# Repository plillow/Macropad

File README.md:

# Macropad
My Macropad, First time ever creating something 
3 keys to be used for anything
Cad image

Pcb 
Schematic

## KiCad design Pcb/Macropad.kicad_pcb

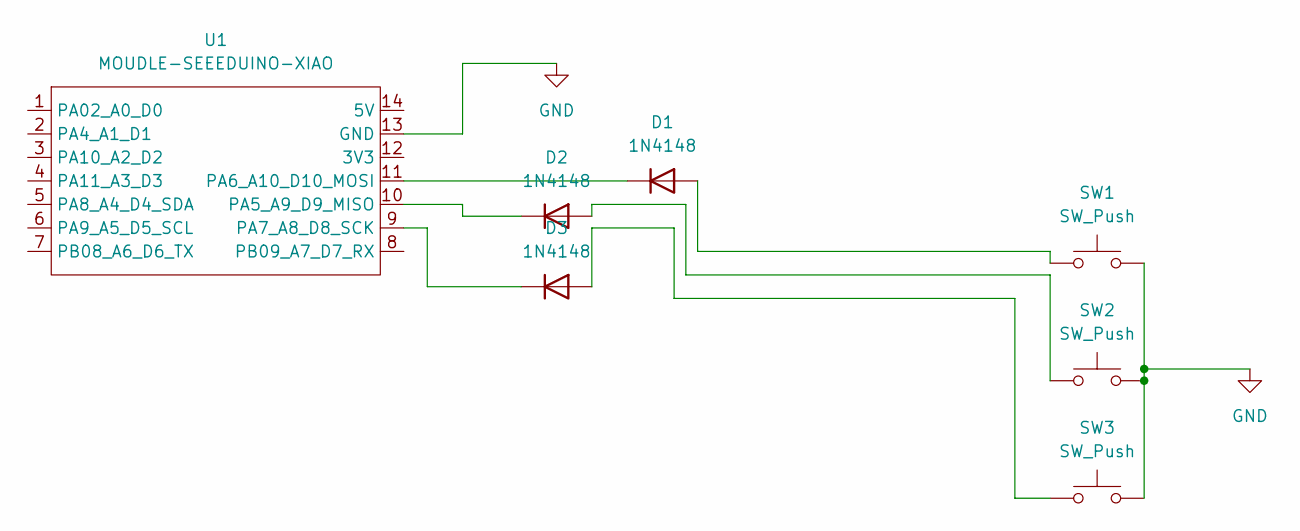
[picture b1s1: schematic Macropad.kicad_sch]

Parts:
D1, D2, D3: 1N4148; D_DO-35_SOD27_P7.62mm_Horizontal
SW1, SW2, SW3: SW_Push; SW_Cherry_MX_1.00u_PCB
U1: MOUDLE-SEEEDUINO-XIAO; MCU_Seeed_ESP32C3

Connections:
GND: SW1.2, SW2.2, SW3.2, U1.13 (GND)
unnamed: D1.2 (A), SW1.1
unnamed: D1.1 (K), U1.11 (PA6_A10_D10_MOSI)
unnamed: D2.2 (A), SW2.1
unnamed: D2.1 (K), U1.10 (PA5_A9_D9_MISO)
unnamed: D3.2 (A), SW3.1
unnamed: D3.1 (K), U1.9 (PA7_A8_D8_SCK)

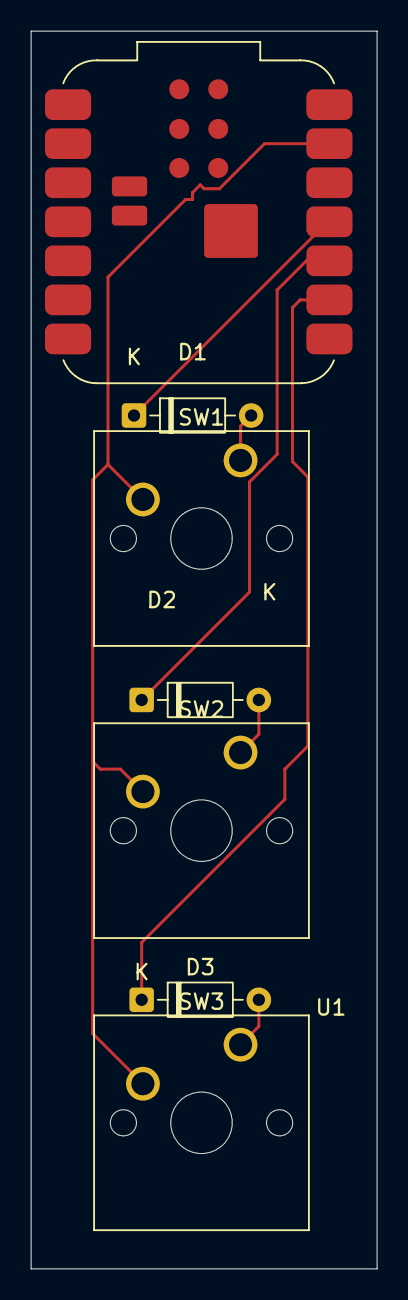
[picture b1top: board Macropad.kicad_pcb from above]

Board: 2 copper layers, 22.5 x 80.5 mm, 7 parts (0 on the bottom side), 7 nets.
